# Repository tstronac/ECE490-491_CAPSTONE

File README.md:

# ECE490-491_CAPSTONE
Capstone project for my EE degree 
Designed and built an IoT Ultraviolet (UV) fire sensing device to identify and extinguish wildfire entering a community, using LoRaWAN protocol 
Designed both the sensor units  (a Sprinkler unit and a UV sensor unit), designed a UV wave guide to increase range of sensor.
We used a RAK3272s for the LoRa Communication, and an STM32 board for the control side of things. 

The sensor board has a solar charger circuitry available, I used the design from the sunnybuddy by sparkfun (under a Beerware license 🍻), and made some adjustments as neccesary.

You can find the schematics below and pics of it working.
Enjoy!!!

(Note: V3 is current)

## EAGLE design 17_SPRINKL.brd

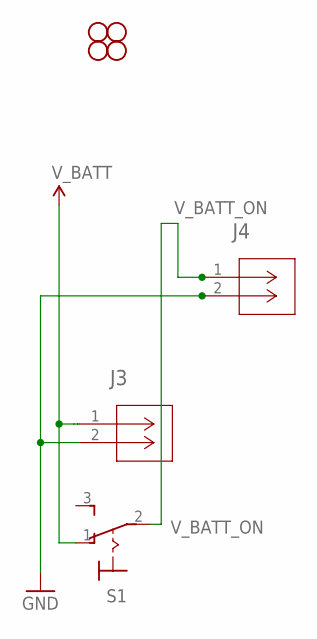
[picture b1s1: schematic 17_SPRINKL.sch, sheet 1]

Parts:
J3, J4: 1729128; CONN_1729128_PXC
S1: M9040P
STANDOFF1, STANDOFF2, STANDOFF3, STANDOFF4: STAND-OFF

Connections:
GND: J3.2, J4.2; also elsewhere on the board
V_BATT: J3.1, S1.1 (O)
V_BATT_ON: J4.1, S1.2; also elsewhere on the board

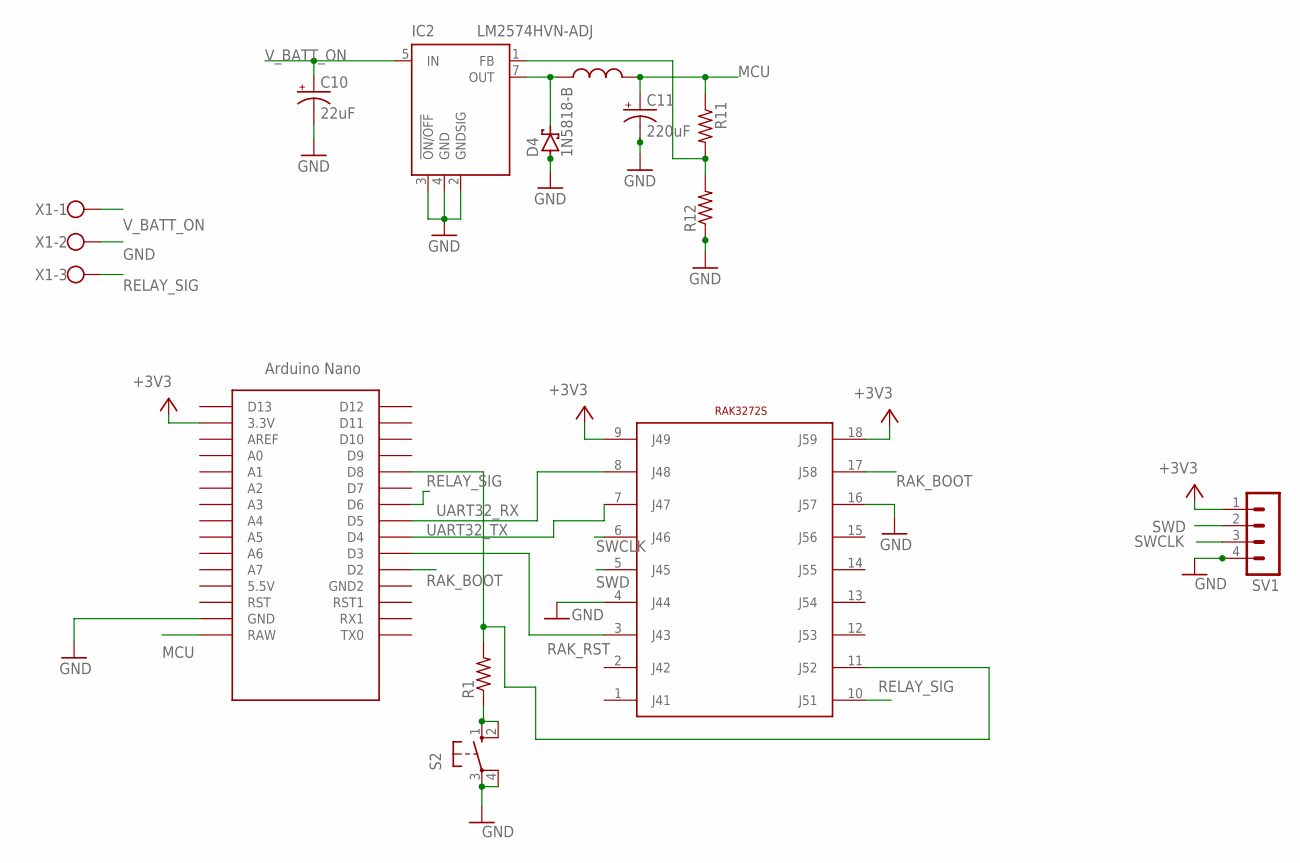
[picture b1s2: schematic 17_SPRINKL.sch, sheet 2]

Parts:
C10: 22uF; E5-6
C11: 220uF; E5-6
D4: 1N5818-B; DO41-7.6
IC2: LM2574HVN-ADJ; DIL08
R1, R11, R12: R-US_0204/7; 0204/7
S2: 10-XX; B3F-10XX
SV1: MA04-1
U$1: 330UH_INDUCTOR
U$3: NANO
U$4: RAK3272S; RAK3272SFOOTPRINT
X1: W237-103

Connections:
+3V3: SV1.1, U$3.3.3V, U$4.9 (J49), U$4.18 (J59)
GND: C10.-, C11.-, D4.A, IC2.2 (GNDSIG), IC2.3 (!ON/OFF), IC2.4 (GND), R12.1, S2.3, S2.4 (P1), SV1.4, U$3.GND, U$4.4 (J44), U$4.16 (J57), X1.2; also elsewhere on the board
MCU: C11.+, R11.1, U$1.P$2, U$3.RAW
unnamed: D4.C, IC2.7 (OUT), U$1.P$1
unnamed: R1.1, S2.1 (S), S2.2 (S1)
unnamed: IC2.1 (FB), R11.2, R12.2
unnamed: R1.2, U$3.D8, U$4.11 (J52)
RAK_BOOT: U$3.D2, U$4.17 (J58)
RAK_RST: U$3.D3, U$4.3 (J43)
RELAY_SIG: U$3.D6, U$4.10 (J51), X1.3
SWCLK: SV1.3, U$4.6 (J46)
SWD: SV1.2, U$4.5 (J45)
UART32_RX: U$3.D4, U$4.7 (J47)
UART32_TX: U$3.D5, U$4.8 (J48)
V_BATT_ON: C10.+, IC2.5 (IN), X1.1; also elsewhere on the board

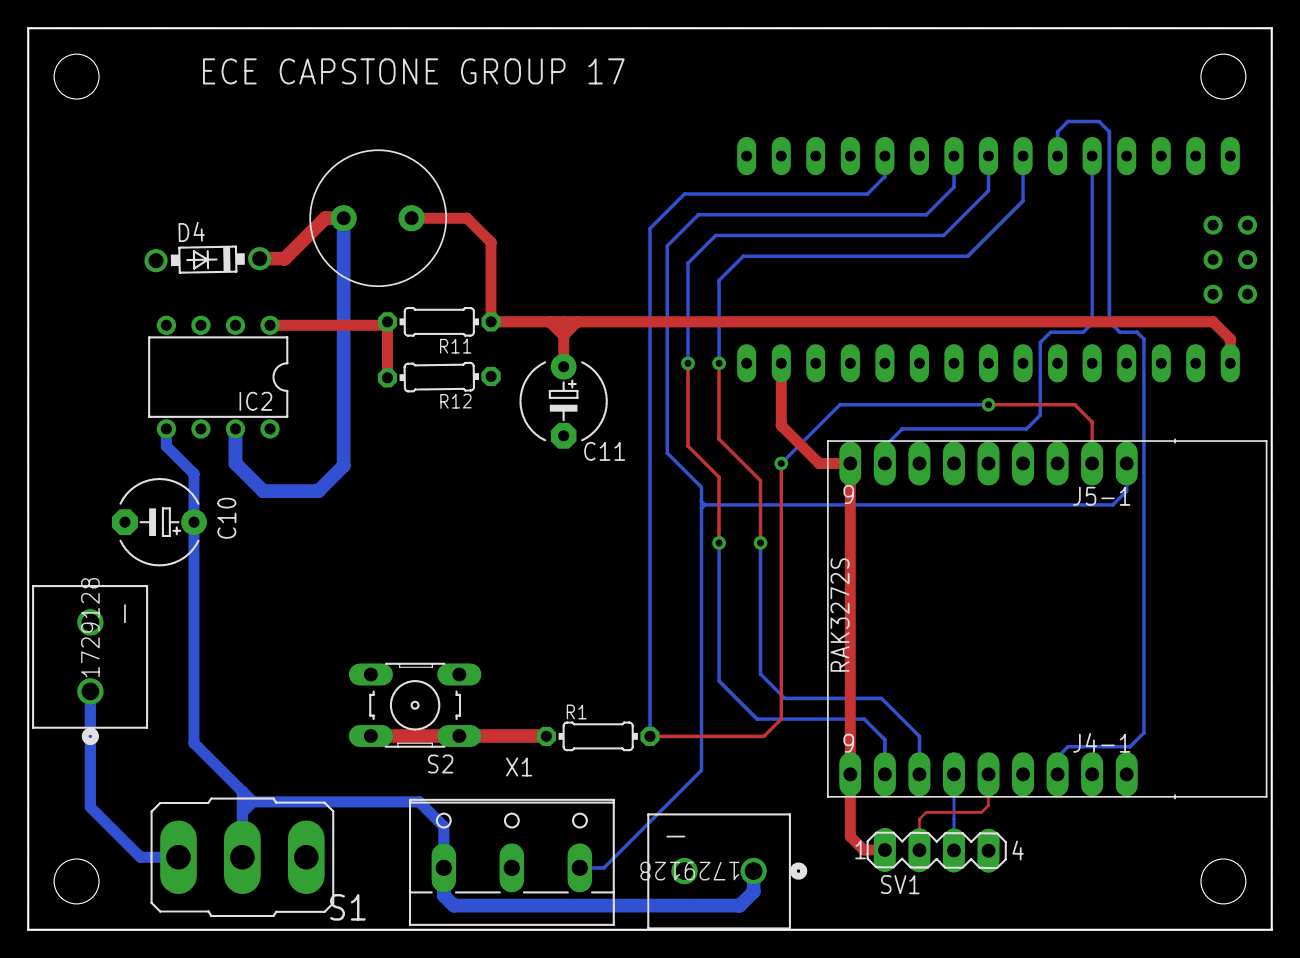
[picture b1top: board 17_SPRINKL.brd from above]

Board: 2 copper layers, 91.4 x 66.3 mm, 20 parts (0 on the bottom side), 16 nets.

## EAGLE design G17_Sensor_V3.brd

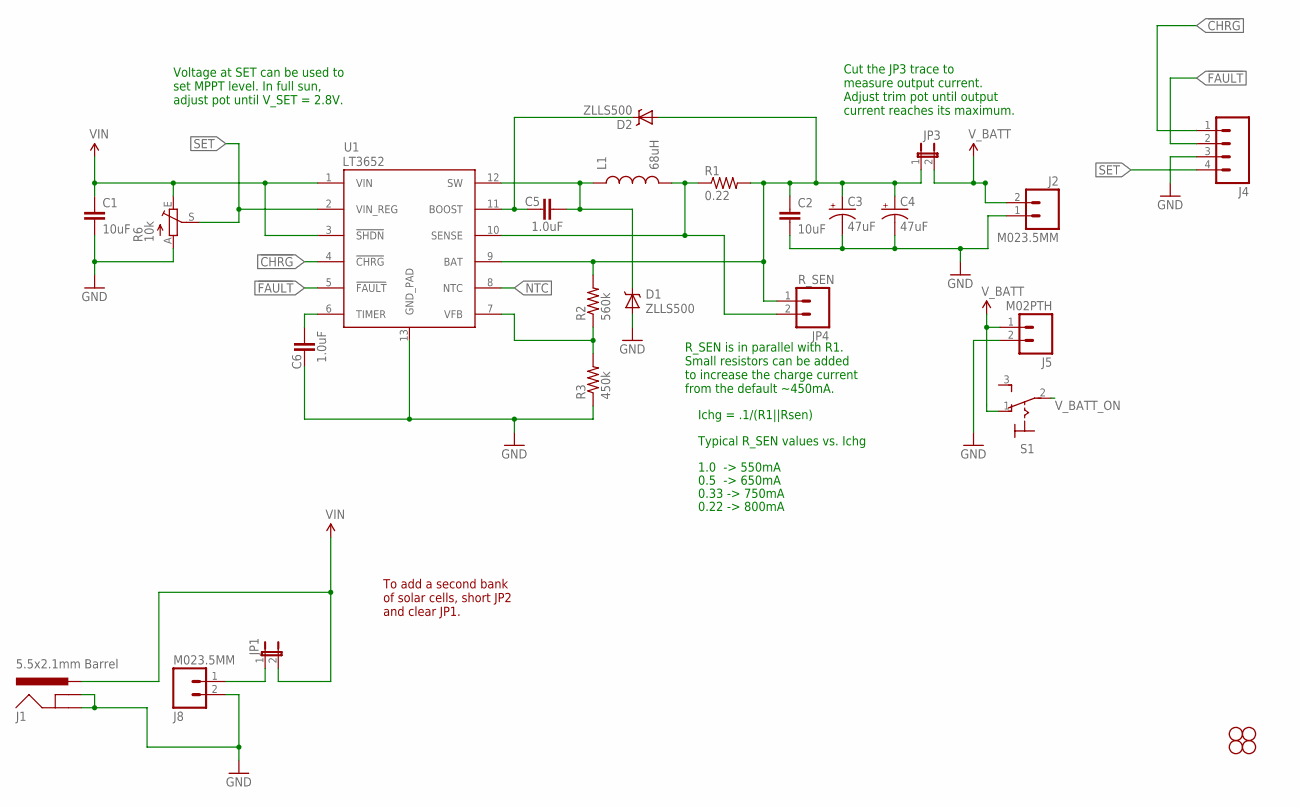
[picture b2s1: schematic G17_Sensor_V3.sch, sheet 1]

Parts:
C1: 10uF; 1210
C2: 10uF; 1206
C3, C4: 47uF; EIA3528
C5, C6: 1.0uF; 0603-CAP
D1, D2: ZLLS500; SOT23
J1: 5.5x2.1mm Barrel; POWER_JACK_SMD
J2, J8: M023.5MM; SCREWTERMINAL-3.5MM-2
J4: M04PTH; 1X04
J5: M02PTH; 1X02
JP1: JUMPER-2SMD-NC; SJ_2S
JP3: JUMPER-PTH-2-NC; PTH-JUMPER-NC_BOTTOM_NO_SILK
JP4: R_SEN; 1X02
L1: 68uH; CR75
R1: 0.22; 0805
R2: 560k; 0603-RES
R3: 450k; 0603-RES
R6: 10k; S63S
S1: M9040P
STANDOFF1, STANDOFF2, STANDOFF3, STANDOFF4: STAND-OFF
U1: LT3652; MSOP-12_GND

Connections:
!CHRG: J4.1, U1.4 (!CHRG)
!FAULT: J4.2, U1.5 (!FAULT)
BOOST: C5.1, D2.3 (C), U1.11 (BOOST)
FB: R2.1, R3.2, U1.7 (VFB)
GND: C1.2, C2.2, C3.C (-), C4.C (-), C6.1, D1.1 (A), J1.GND (GNDBREAK), J1.P$4 (GND), J2.1, J4.3, J5.2, J8.2, R3.1, R6.A, U1.13 (GND_PAD); also elsewhere on the board
unnamed: C2.1, C3.A (+), C4.A (+), D2.1 (A), JP3.1, JP4.1, R1.2, R2.2, U1.9 (BAT)
unnamed: J8.1, JP1.1
NTC: U1.8 (NTC)
SENSE: JP4.2, L1.P$2 (2), R1.1, U1.10 (SENSE)
SET: J4.4, R6.S, U1.2 (VIN_REG)
SW: C5.2, D1.3 (C), L1.P$1 (1), U1.12 (SW)
TIMER: C6.2, U1.6 (TIMER)
VIN: C1.1, J1.VIN0 (PWR), JP1.2, R6.E, U1.1 (VIN), U1.3 (!SHDN)
V_BATT: J2.2, J5.1, JP3.2, S1.1 (O)
V_BATT_ON: S1.2; also elsewhere on the board

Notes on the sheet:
To add a second bank of solar cells, short JP2 and clear JP1.
Cut the JP3 trace to measure output current. Adjust trim pot until output current reaches its maximum.
R_SEN is in parallel with R1. Small resistors can be added to increase the charge current from the default ~450mA.
0.22 -> 800mA
Ichg = .1/(R1||Rsen)
Typical R_SEN values vs. Ichg
1.0 -> 550mA
0.33 -> 750mA
0.5 -> 650mA
Voltage at SET can be used to set MPPT level. In full sun, adjust pot until V_SET = 2.8V.

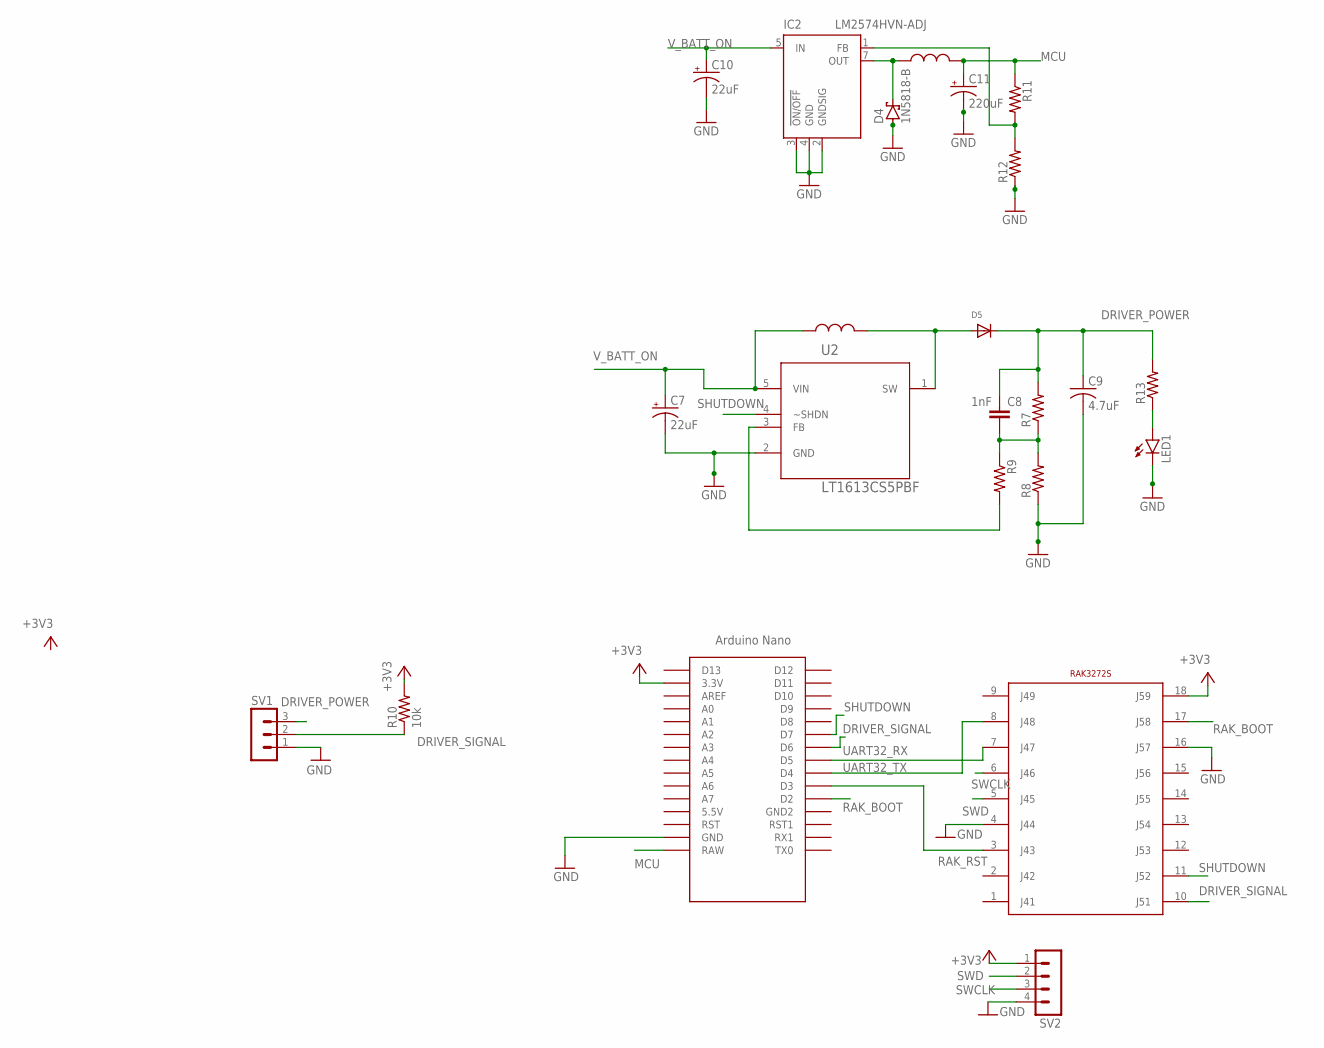
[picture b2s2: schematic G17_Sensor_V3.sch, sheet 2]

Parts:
C7, C10: 22uF; E5-6
C8: 1nF; C5B2.5
C9: 4.7uF; C025-024X044
C11: 220uF; E5-6
D4: 1N5818-B; DO41-7.6
D5: DIODESOD-123; SOD-123
IC2: LM2574HVN-ADJ; DIL08
LED1: LED5MM
R7, R8, R9, R13: R-US_0204/5; 0204/5
R10: 10k; 0204/5
R11, R12: R-US_0204/7; 0204/7
SV1: MA03-1
SV2: MA04-1
U2: LT1613CS5PBF; SOT95P280X145-5N
U$1, U$2: 330UH_INDUCTOR
U$3: NANO
U$4: RAK3272S; RAK3272SFOOTPRINT

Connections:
+3V3: R10.2, SV2.1, U$3.3.3V, U$4.18 (J59)
DRIVER_POWER: C8.1, C9.1, D5.C, R7.2, R13.2, SV1.3
DRIVER_SIGNAL: R10.1, SV1.2, U$3.D6, U$4.10 (J51)
GND: C7.-, C9.2, C10.-, C11.-, D4.A, IC2.2 (GNDSIG), IC2.3 (!ON/OFF), IC2.4 (GND), LED1.K (C), R8.1, R12.1, SV1.1, SV2.4, U2.2 (GND), U$3.GND, U$4.4 (J44), U$4.16 (J57); also elsewhere on the board
MCU: C11.+, R11.1, U$1.P$2, U$3.RAW
unnamed: IC2.1 (FB), R11.2, R12.2
unnamed: R9.2, U2.3 (FB)
unnamed: D5.A, U2.1 (SW), U$2.P$2
unnamed: D4.C, IC2.7 (OUT), U$1.P$1
unnamed: C8.2, R7.1, R8.2, R9.1
unnamed: LED1.A, R13.1
RAK_BOOT: U$3.D2, U$4.17 (J58)
RAK_RST: U$3.D3, U$4.3 (J43)
SHUTDOWN: U2.4 (~SHDN), U$3.D7, U$4.11 (J52)
SWCLK: SV2.3, U$4.6 (J46)
SWD: SV2.2, U$4.5 (J45)
UART32_RX: U$3.D5, U$4.7 (J47)
UART32_TX: U$3.D4, U$4.8 (J48)
V_BATT_ON: C7.+, C10.+, IC2.5 (IN), U2.5 (VIN), U$2.P$1; also elsewhere on the board

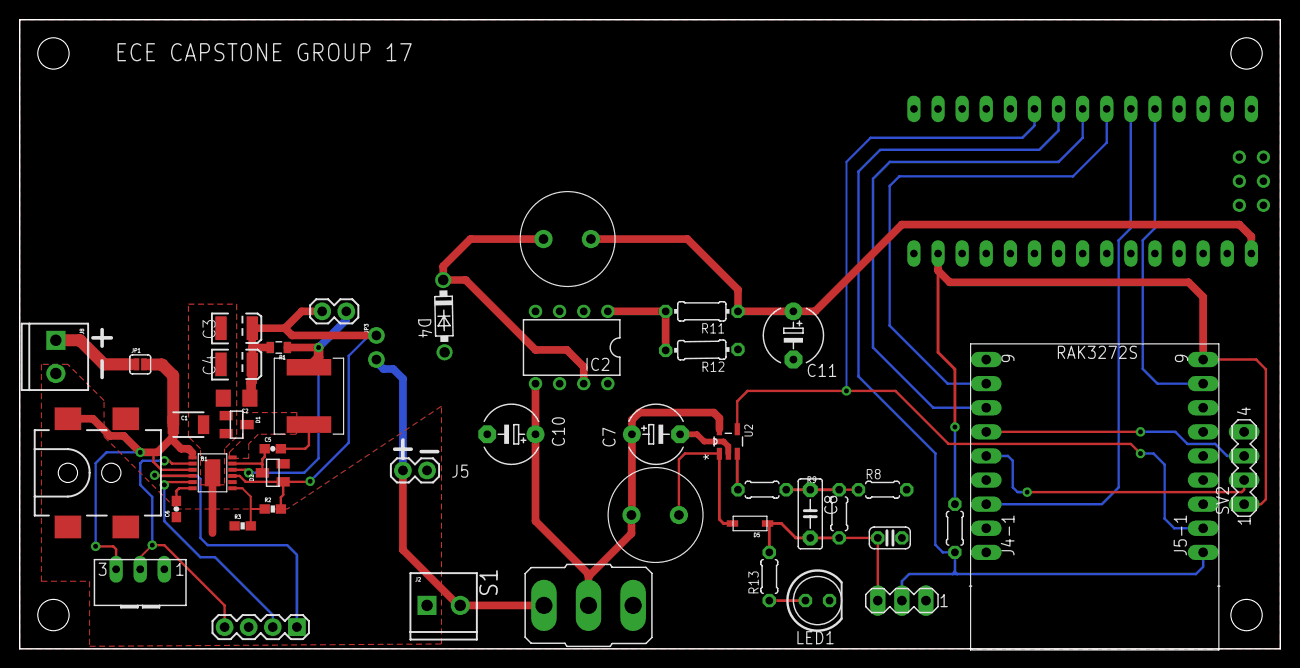
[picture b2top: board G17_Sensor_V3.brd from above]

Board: 2 copper layers, 132.8 x 66.3 mm, 50 parts (0 on the bottom side), 31 nets.

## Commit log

2023-02-21 Create Test
    Making Folders cause Git flipped a bit
2023-02-21 actual work here
    work is here
2023-02-21 Add files via upload
    ThEGoOdsTuFf
2023-02-24 needs jumpers for UV sensor/ RAK needs traces. All else is set up
2023-08-17 finally a description about this stuff
2023-08-17 forgot about the sunny buddy
2023-08-17 Sprinkler Board stuff
    Credit to Serena Nguyen-Vu and Timothy Stronach
2023-08-17 naming versions

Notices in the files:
parts and their libraries:
SparkFun-Electromechanical: Licensing: CC v3.0 Share-Alike You are welcome to use this library for commercial purposes.
COPYRIGHT: Copyright (C) 2023 Ultra Librarian. All rights reserved.
